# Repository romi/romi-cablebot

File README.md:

# Romi Cablebot (v2)

Documentation coming soon...

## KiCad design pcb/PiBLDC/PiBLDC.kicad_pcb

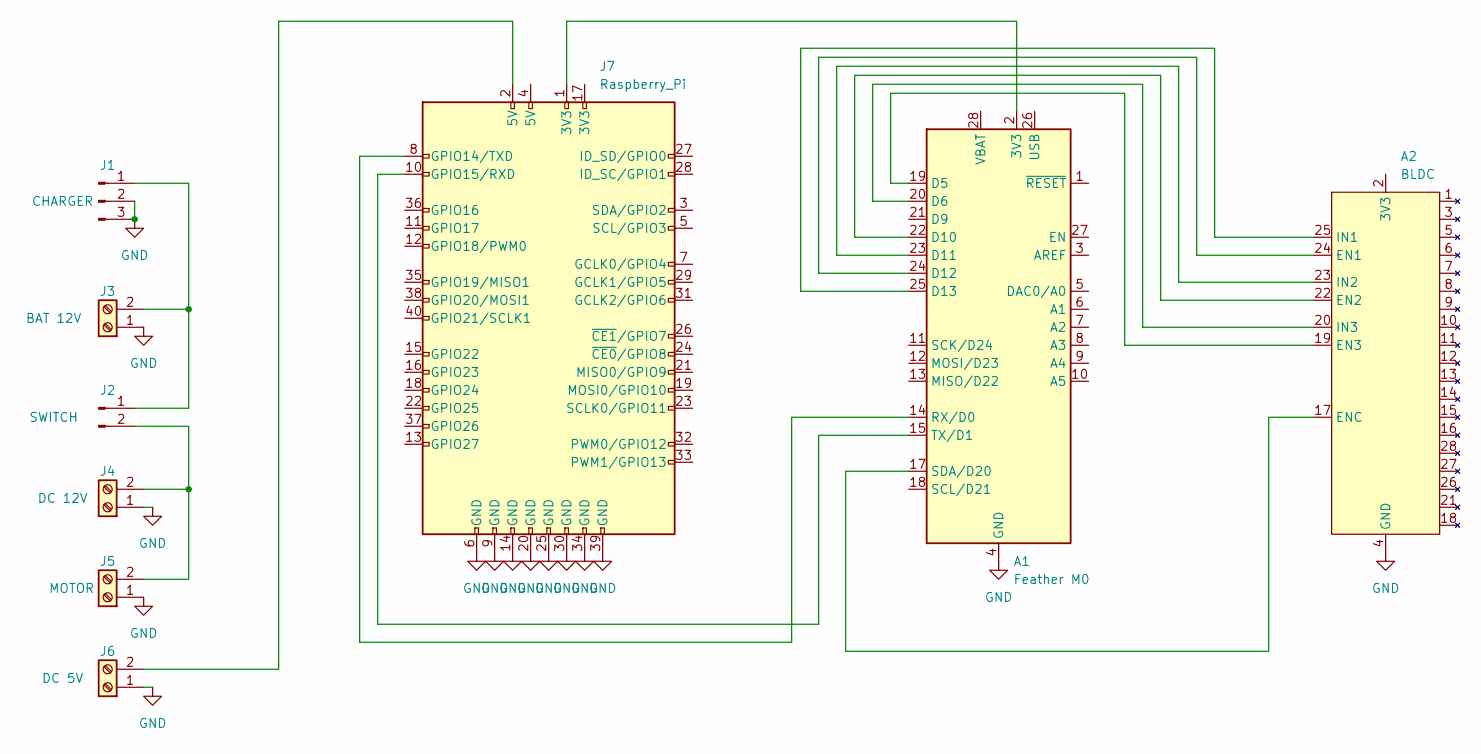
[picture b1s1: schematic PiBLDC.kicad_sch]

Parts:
A1: Feather M0; Adafruit_Feather
A2: BLDC; Adafruit_Feather
J1: CHARGER; Molex_Micro-Fit_3.0_43650-0300_1x03_P3.00mm_Horizontal
J2: SWITCH; Molex_Micro-Fit_3.0_43650-0200_1x02_P3.00mm_Horizontal
J3: BAT 12V; TerminalBlock_Phoenix_PT-1,5-2-3.5-H_1x02_P3.50mm_Horizontal
J4: DC 12V; TerminalBlock_Phoenix_PT-1,5-2-3.5-H_1x02_P3.50mm_Horizontal
J5: MOTOR; TerminalBlock_Phoenix_PT-1,5-2-3.5-H_1x02_P3.50mm_Horizontal
J6: DC 5V; TerminalBlock_Phoenix_PT-1,5-2-3.5-H_1x02_P3.50mm_Horizontal
J7: Raspberry_Pi; PinHeader_2x20_P2.54mm_Vertical

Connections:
GND: A1.4 (GND), A1.16 (GND), A2.4 (GND), J1.2, J1.3, J3.1, J4.1, J5.1, J6.1, J7.6 (GND), J7.9 (GND), J7.14 (GND), J7.20 (GND), J7.25 (GND), J7.30 (GND), J7.34 (GND), J7.39 (GND)
unnamed: A1.2 (3V3), J7.1 (3V3)
unnamed: A1.14 (RX/D0), J7.8 (GPIO14/TXD)
unnamed: A1.15 (TX/D1), J7.10 (GPIO15/RXD)
unnamed: A1.17 (SDA/D20), A2.17 (ENC)
unnamed: A1.19 (D5), A2.19 (EN3)
unnamed: A1.20 (D6), A2.20 (IN3)
unnamed: A1.22 (D10), A2.22 (EN2)
unnamed: A1.23 (D11), A2.23 (IN2)
unnamed: A1.24 (D12), A2.24 (EN1)
unnamed: A1.25 (D13), A2.25 (IN1)
unnamed: J1.1, J2.1, J3.2
unnamed: J2.2, J4.2, J5.2
unnamed: J6.2, J7.2 (5V)

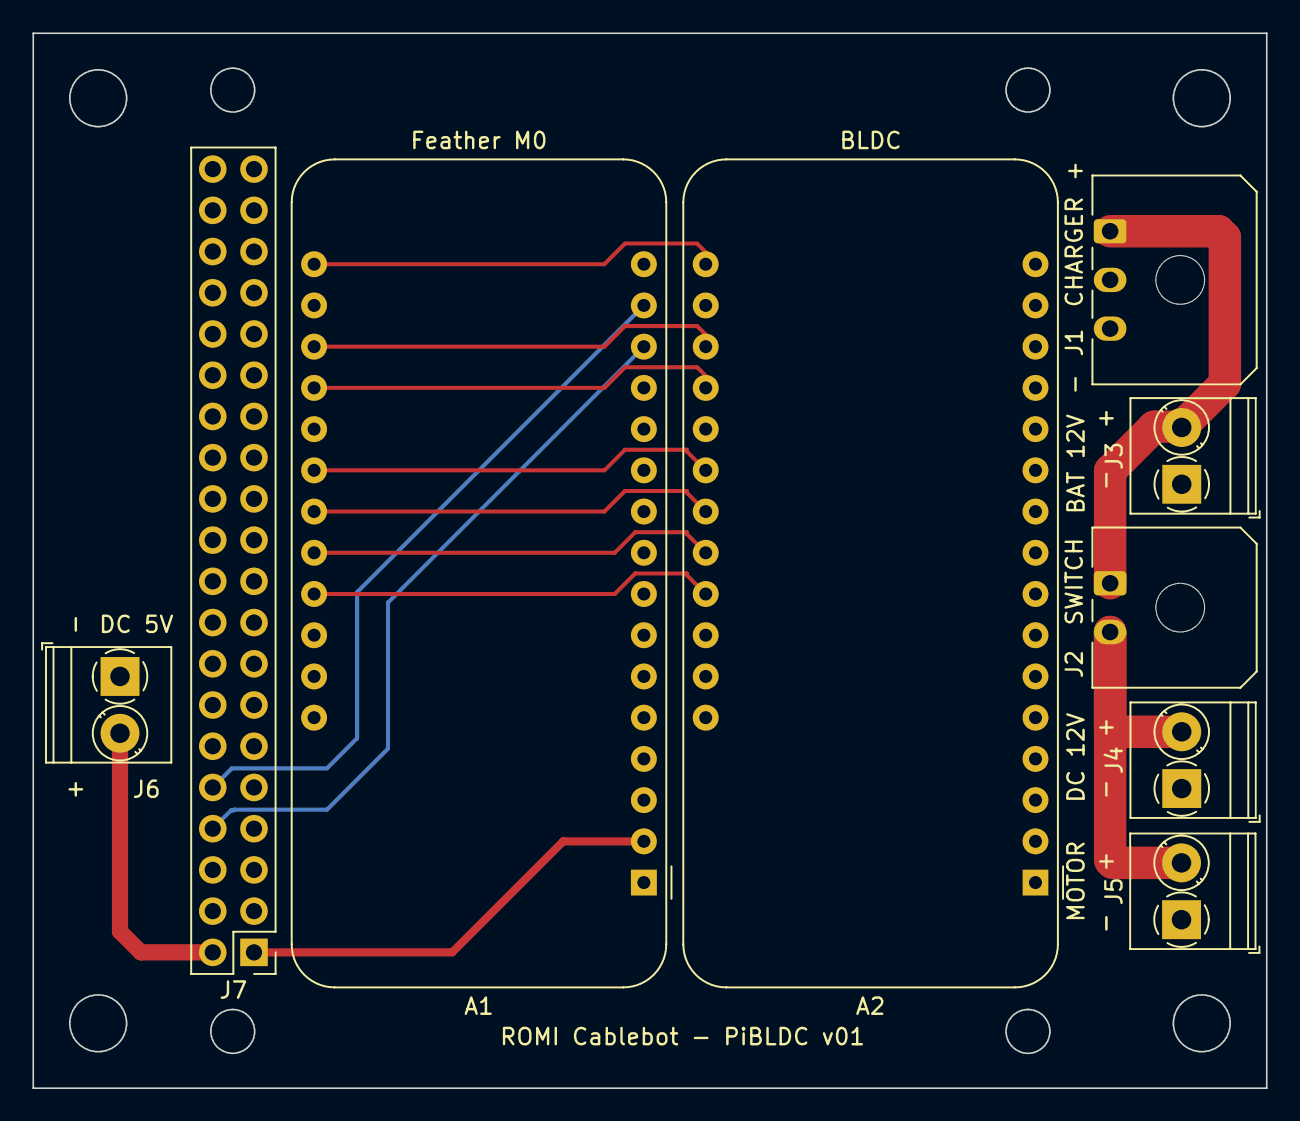
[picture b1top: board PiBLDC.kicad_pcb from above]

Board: 2 copper layers, 76.0 x 65.0 mm, 9 parts (0 on the bottom side), 14 nets.

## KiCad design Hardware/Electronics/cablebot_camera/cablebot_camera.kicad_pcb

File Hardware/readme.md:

# Cablebot hardware

## Head
### 3d printed PLA

|       |                                                                      |
| :---: | ---                                                                  |
| 1x    | [Encoder cap](./3d-Print/Cablebot-Encoder_cap.stl)                   |
| 1x    | [Head separator front](./3d-Print/Cablebot-Head_separator_front.stl) |
| 1x    | [Head separator up](./3d-Print/Cablebot-Head_separator_up.stl)       |
| 1x    | [Spring holder up](./3d-Print/Cablebot-Spring_holder_Up.stl)         |
| 1x    | [Head separator back](./3d-Print/Cablebot-Head_separator_back.stl)   |
| 1x    | [Encoder holder](./3d-Print/Cablebot-Encoder_holder.stl)             |

### Milled Alucobond

|       |                                                                        |
| :---: | ---                                                                    |
| 1x    | [Head front](./Milled-Alucobond/Cablebot-Head_front.dxf)               |
| 1x    | [Head middle front](./Milled-Alucobond/Cablebot-Head_middle_front.dxf) |
| 1x    | [Head middle back](./Milled-Alucobond/Cablebot-Head_middle_back.dxf)   |
| 1x    | [Head back](./Milled-Alucobond/Cablebot-Head_back.dxf)                 |

## Arms
### 3d printed PLA

|       |                                                                              |
| :---: | ---                                                                          |
| 1x    | [Left arm cap out](./3d-Print/Cablebot-Left_arm_cap_out.stl)                 |
| 1x    | [Pogo pin clip](./3d-Print/Cablebot-Pogo_pin_clip.stl)                       |
| 1x    | [Left arm cap middle](./3d-Print/Cablebot-Left_arm_cap_middle.stl)           |
| 1x    | [Control board pcb holder](./3d-Print/Cablebot-Control_board_pcb_holder.stl) |
| 1x    | [Right arm cap middle](./3d-Print/Cablebot-Right_arm_cap_middle.stl)         |
| 1x    | [Right arm cap out](./3d-Print/Cablebot-Right_arm_cap_out.stl)               |

### Milled Alucobond

|       |                                                                      |
| :---: | ---                                                                  |
| 1x    | [Arm left](./Milled-Alucobond/Cablebot-Arm_left.dxf)                 |
| 4x    | [Arms slider fill](./Milled-Alucobond/Cablebot-Arms_slider_fill.dxf) |
| 4x    | [Arm right](./Milled-Alucobond/Cablebot-Arms_right.dxf)              |

## Hands
### 3d printed PLA

|       |                                                                                    |
| :---: | ---                                                                                |
| 1x    | [Hand end stop trigger left](./3d-Print/Cablebot-Hand_end_stop_trigger_left.stl)   |
| 1x    | [Hand base left](./3d-Print/Cablebot-Hand_base_left.stl)                           |
| 2x    | [Pulley 608zz](./3d-Print/Cablebot-Pulley_608zz.stl)                               |
| 1x    | [Hand base right](./3d-Print/Cablebot-Hand_base_right.stl)                         |
| 1x    | [Hand end stop trigger right](./3d-Print/Cablebot-Hand_end_stop_trigger_right.stl) |

### Milled Alucobond

|       |                                                                                    |
| :---: | ---                                                                                |
| 1x    | [Hand left out small](./Milled-Alucobond/Cablebot-Hand_left_out_small.dxf)         |
| 1x    | [Hand left middle small](./Milled-Alucobond/Cablebot-Hand_left_middle_small.dxf)   |
| 1x    | [Hand front left](./Milled-Alucobond/Cablebot-Hand_front_left.dxf)                 |
| 1x    | [Hand right out small](./Milled-Alucobond/Cablebot-Hand_right_out_small.dxf)       |
| 1x    | [Hand right middle small](./Milled-Alucobond/Cablebot-Hand_right_middle_small.dxf) |
| 1x    | [Hand front right](./Milled-Alucobond/Cablebot-Hand_front_right.dxf)               |
| 1x    | [Hand left out big](./Milled-Alucobond/Cablebot-Hand_left_out_big.dxf)             |
| 1x    | [Hand left middle big](./Milled-Alucobond/Cablebot-Hand_left_middle_big.dxf)       |
| 1x    | [Hand right out big](./Milled-Alucobond/Cablebot-Hand_right_out_big.dxf)           |
| 1x    | [Hand right middle big](./Milled-Alucobond/Cablebot-Hand_right_middle_big.dxf)     |

Just one set is needed either _small_ or _big_, depending on cable tension (big is better for high tension).

## Body 
### 3d printed PLA

|       |                                                                  |
| :---: | ---                                                              |
| 1x    | [Cable bridge left](./3d-Print/Cablebot-Cable_bridge_left.stl)   |
| 1x    | [Spring holder down](./3d-Print/Cablebot-Spring_holder_down.stl) |
| 1x    | [Power pcb holder](./3d-Print/Cablebot-Power_pcb_holder.stl)     |
| 1x    | [Cable bridge right](./3d-Print/Cablebot-Cable_bridge_right.stl) |

### Milled Alucobond

|       |                                                                            |
| :---: | ---                                                                        |
| 1x    | [Body cover back](./Milled-Alucobond/Cablebot-Body_cover_back.dxf)         |
| 1x    | [H holder](./Milled-Alucobond/Cablebot-H_holder.dxf)                       |
| 1x    | [Body cover front](./Milled-Alucobond/Cablebot-Body_cover_front.dxf)       |

## Battery module
### 3d printed PLA

|       |                                                                                           |
| :---: | ---                                                                                       |
| 1x    | [Battery cap](./3d-Print/Cablebot-Battery_cap.stl)                                        |
| 1x    | [Battery and BMS box](./3d-Print/Cablebot-Battery_and_BMS_box.stl)                        |
| 1x    | [Battery connector top](./3d-Print/Cablebot-Battery_connector_top.stl)                    |
| 1x    | [Battery connector bottom](./3d-Print/Cablebot-Battery_connector_bottom.stl)              |

### Milled Alucobond

|       |                                                                            |
| :---: | ---                                                                        |
| 1x    | [Battery cover](./Milled-Alucobond/Cablebot-Battery_cover.dxf)             |

## Camera module
### 3d printed PLA

|       |                                                                     |
| :---: | ---                                                                 |
| 1x    | [Bearing cap](./3d-Print/Camera_module-Bearing_cap.stl)             |
| 1x    | [Main cap](./3d-Print/Camera_module-Main_Cap.stl)                   |
| 1x    | [Pcb holder](./3d-Print/Camera_module-PCB_holder.stl)               |
| 1x    | [Top connector cap](./3d-Print/Camera_module-Top_connector_cap.stl) |
| 1x    | [Corner motor top](./3d-Print/Camera_module-Corner_motor_top.stl)   |

### Milled Alucobond

|       |                                                                     |
| :---: | ---                                                                 |
| 1x    | [Holder top](./Milled-Alucobond/Camera_module-Holder_top.dxf)       |
| 1x    | [Holder bottom](./Milled-Alucobond/Camera_module-Holder_bottom.dxf) |
| 1x    | [Holder camera](./Milled-Alucobond/Camera_module-Holder_camera.dxf) |

## Charging Station hardware

### 3d printed PLA

|		|																	|
| :---: | --- 																|
| 1x 	| [Arc](./3d-Print/Charging_station-Arc.stl)						|
| 1x 	| [Hold roof](./3d-Print/Charging_station-Hold_roof.stl) 			|
| 2x 	| [Caps](./3d-Print/Charging_station-Cap.stl) 						|
| 4x 	| [Cap separator](./3d-Print/Charging_station-Cap_separator.stl) 	|

### Milled Alucobond

|       |                                                                     |
| :---: | ---                                                                 |
| 1x    | [Back](./Milled-Alucobond/Charging_station-Back.dxf)       		  |
| 1x    | [Roof](./Milled-Alucobond/Charging_station-Roof.dxf) 		   		  |
| 1x    | [Side left](./Milled-Alucobond/Charging_station-Sides.dxf)  		  |
| 1x    | [Side right](./Milled-Alucobond/Charging_station-Sides.dxf) 		  |

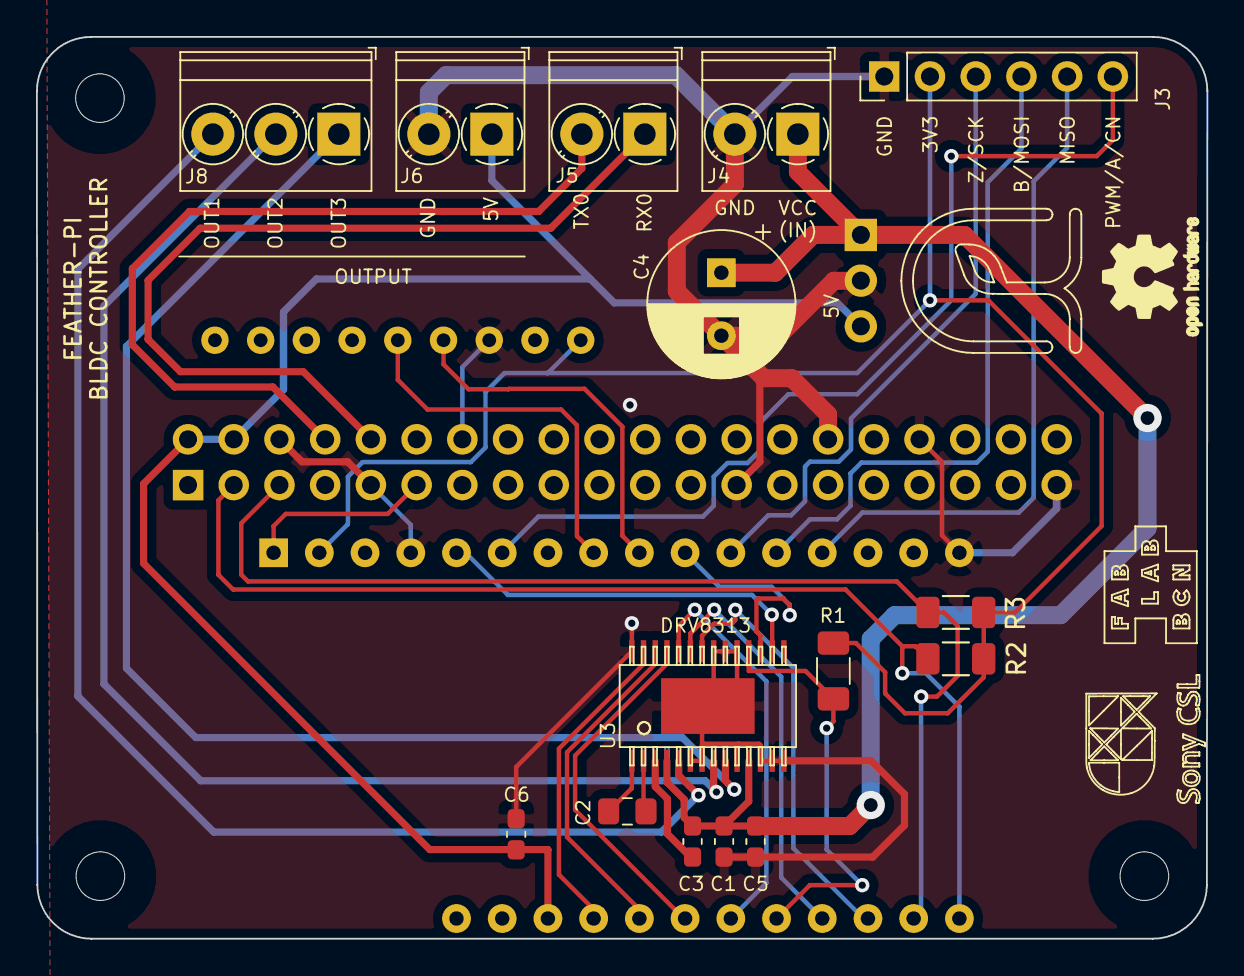
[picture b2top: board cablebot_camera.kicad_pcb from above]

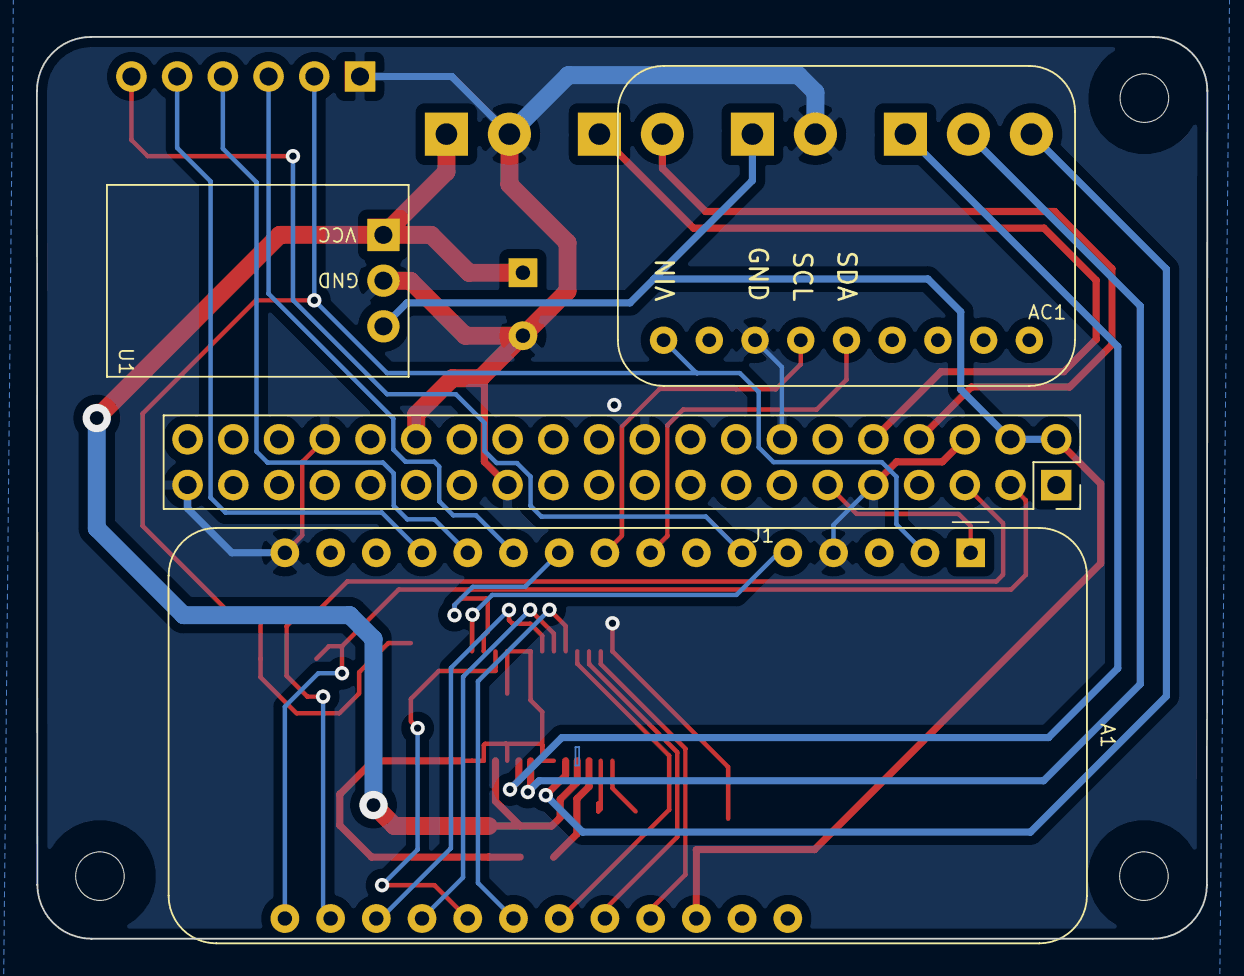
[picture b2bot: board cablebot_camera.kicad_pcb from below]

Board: 2 copper layers, 65.0 x 50.1 mm, 26 parts (4 on the bottom side), 31 nets.

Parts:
A1: Adafruit_Feather_M0_Express; Adafruit_Feather
AC1: ACCEL; Adafruit-LSM6DSOX-PCB
C1, C3, C5, C6: 0.1uF; C_0603_1608Metric_Pad1.08x0.95mm_HandSolder
C2: 0.01uF; C_0805_2012Metric_Pad1.18x1.45mm_HandSolder
C4: 100uF; CP_Radial_D8.0mm_P3.50mm
H3, H4, H6: MountingHole; MountingHole_2.7mm_M2.5_uHAT_RPi
J1: GPIO_CONNECTOR; PinSocket_2x20_P2.54mm_Vertical_Centered_Anchor
J3: Conn_01x06_Male; PinHeader_1x06_P2.54mm_Vertical
J4, J5, J6: Screw_Terminal_01x02; TerminalBlock_Phoenix_PT-1,5-2-3.5-H_1x02_P3.50mm_Horizontal
J8: Screw_Terminal_01x03; TerminalBlock_Phoenix_PT-1,5-3-3.5-H_1x03_P3.50mm_Horizontal
LOGO1: Logo_Open_Hardware_Small; OSHW-Logo2_7.3x6mm_SilkScreen
LOGO2: fablab
LOGO3: ROMI; ROMI_LOGO
LOGO4: SONYLOGO; SONY_CSL_LOGO
R1, R2, R3: 10kΩ; R_1206_3216Metric_Pad1.30x1.75mm_HandSolder
U1: OKI-78SR-5_1.5-W36-C; Converter_DCDC_Murata_OKI-78SR_Horizontal
U3: DRV8313; SquantorTexasInstruments-HTSSOP-28

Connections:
3V3: A1.2, AC1.1, J3.2, R1.2, R2.1, R3.1
5V: A1.26, C6.2, J1.2, J1.4, J6.1, U1.3
+3V3: J1.1, J1.17
CN_PWM_A: A1.6, J3.6
EN1: A1.24, U3.26
EN2: A1.22, U3.24
EN3: A1.19, U3.22
FAULT: A1.21, R1.1, U3.18
FEATHER_RESET: A1.1, J1.11
GND: A1.4, A1.16, AC1.3, C1.1, C4.2, C5.1, C6.1, J1.6, J1.9, J1.14, J1.20, J1.25, J1.30, J1.34, J1.39, J3.1, J4.2, J6.2, U1.2, U3.6, U3.7, U3.10, U3.12, U3.13, U3.14, U3.19, U3.20, U3.21, U3.28, U3.PAD
IN1: A1.25, U3.27
IN2: A1.23, U3.25
IN3: A1.20, U3.23
MISO: A1.13, J3.5
MOSI_B: A1.12, J3.4
unnamed: C2.1, U3.1
unnamed: C2.2, U3.2
unnamed: C3.2, U3.3
OUT1: J8.3, U3.5
OUT2: J8.2, U3.8
OUT3: J8.1, U3.9
RESET: A1.5, U3.16
RX0: J1.10, J5.1
SCK_Z: A1.11, J3.3
SCL: A1.18, J1.5, R3.2
SCL_IMU: A1.9, AC1.4
SDA: A1.17, J1.3, R2.2
SDA_IMU: A1.8, AC1.5
SLEEP: A1.10, U3.17
TX0: J1.8, J5.2
VCC: C1.2, C3.1, C4.1, C5.2, J4.1, U1.1, U3.4, U3.11

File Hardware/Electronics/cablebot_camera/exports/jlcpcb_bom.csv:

Comment,Designator,Footprint,LCSC
"Adafruit_Feather_M0_Express","A1","Module:Adafruit_Feather",""
"ACCEL","AC1","fab:Adafruit-LSM6DSOX-PCB",""
"0.01uF","C2","Capacitor_SMD:C_0805_2012Metric_Pad1.18x1.45mm_HandSolder","C28233"
"0.1uF","C1,C3,C5,C6","Capacitor_SMD:C_0603_1608Metric_Pad1.08x0.95mm_HandSolder","C14663"
"100uF","C4","Capacitor_THT:CP_Radial_D8.0mm_P3.50mm",""
"MountingHole","H3,H4,H6","lib:MountingHole_2.7mm_M2.5_uHAT_RPi",""
"GPIO_CONNECTOR","J1","lib:PinSocket_2x20_P2.54mm_Vertical_Centered_Anchor",""
"Conn_01x06_Male","J3","Connector_PinHeader_2.54mm:PinHeader_1x06_P2.54mm_Vertical",""
"Screw_Terminal_01x02","J4,J5,J6","TerminalBlock_Phoenix:TerminalBlock_Phoenix_PT-1,5-2-3.5-H_1x02_P3.50mm_Horizontal",""
"Screw_Terminal_01x03","J8","TerminalBlock_Phoenix:TerminalBlock_Phoenix_PT-1,5-3-3.5-H_1x03_P3.50mm_Horizontal",""
"Logo_Open_Hardware_Small","LOGO1","Symbol:OSHW-Logo2_7.3x6mm_SilkScreen",""
"fablab","LOGO2","logos:fablab",""
"ROMI","LOGO3","logos:ROMI_LOGO",""
"SONYLOGO","LOGO4","logos:SONY_CSL_LOGO",""
"10kΩ","R1,R2,R3","Resistor_SMD:R_1206_3216Metric_Pad1.30x1.75mm_HandSolder",""
"OKI-78SR-5_1.5-W36-C","U1","Converter_DCDC:Converter_DCDC_Murata_OKI-78SR_Horizontal",""
"DRV8313","U3","SquantorTexasInstruments:SquantorTexasInstruments-HTSSOP-28","C92482"

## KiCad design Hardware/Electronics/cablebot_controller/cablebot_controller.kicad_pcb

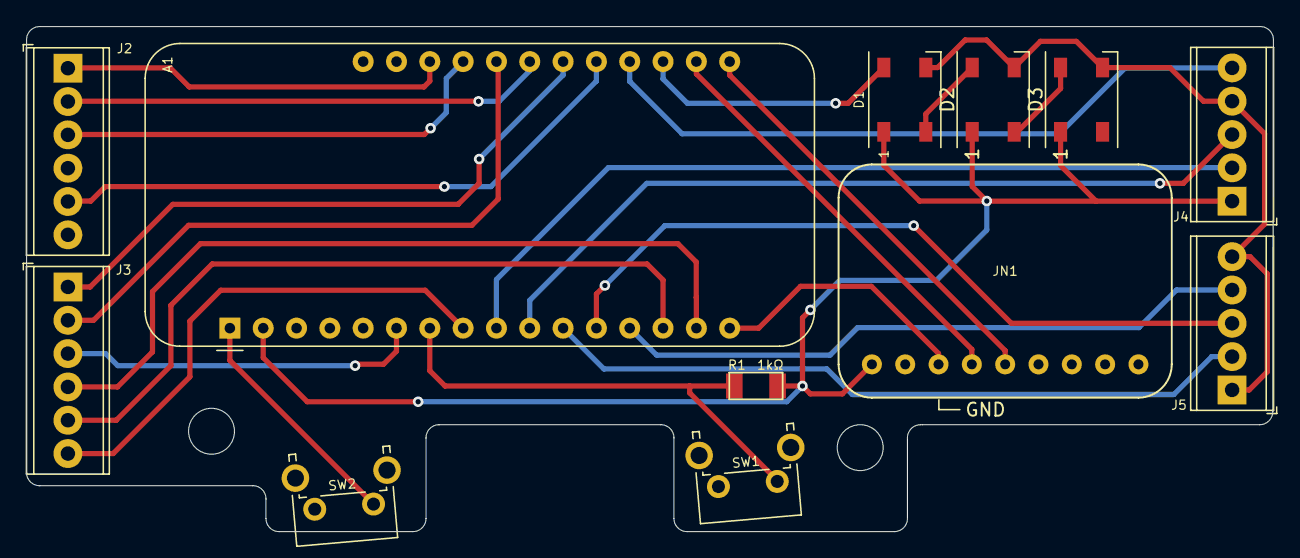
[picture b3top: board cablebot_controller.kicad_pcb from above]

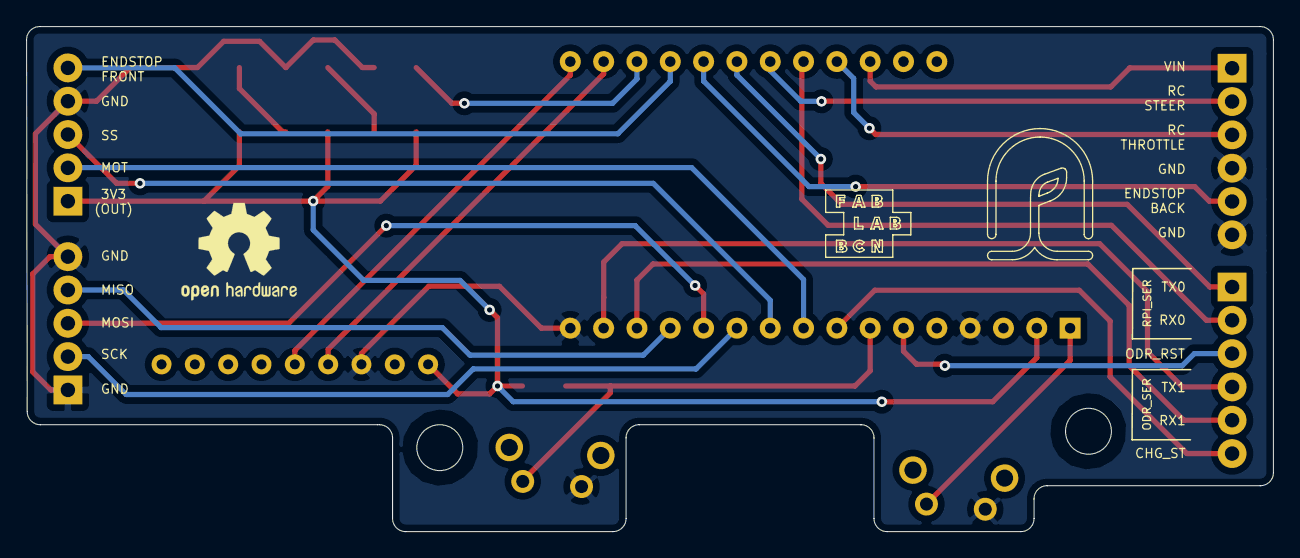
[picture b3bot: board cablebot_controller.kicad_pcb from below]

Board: 2 copper layers, 95.1 x 38.5 mm, 15 parts (3 on the bottom side), 25 nets.

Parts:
A1: Adafruit_Feather_M0_Basic_Proto; Adafruit_Feather
D1, D2, D3: WS2812B; LED_WS2812B_PLCC4_5.0x5.0mm_P3.2mm
J2, J3: Screw_Terminal_01x06; TerminalBlock_Phoenix_MPT-0,5-6-2.54_1x06_P2.54mm_Horizontal
J4, J5: Screw_Terminal_01x05; TerminalBlock_Phoenix_MPT-0,5-5-2.54_1x05_P2.54mm_Horizontal
JN1: ACCEL; Adafruit-LSM6DSOX-PCB
OSH1: Logo_Open_Hardware_Small; OSHW-Logo2_9.8x8mm_SilkScreen
R1: 1kΩ; fab-R1206FAB
SW1: SW_SPST; SW_Tactile_SPST_Angled_PTS645Vx83-2LFS
SW2: SW_SPST; SW_Tactile_SPST_Angled_PTS645Vx58-2LFS
U1: fablab
U2: romi; ROMI_LOGO

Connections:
3V3: A1.2, D1.1, D2.1, D3.1, J4.1, JN1.1, R1.1
5V: A1.26, J2.1
ADNS_MOT: A1.9, J4.2
ADNS_SS: A1.10, J4.3
CHG_ST_HOME: A1.8, J3.6
ENDSTOP_BACK: A1.21, J2.5
ENDSTOP_FRONT: A1.20, J4.5
GND: A1.4, A1.16, D1.3, D2.3, D3.3, J2.4, J2.6, J4.4, J5.1, J5.5, JN1.3, SW1.2, SW2.2
LED_DIN: A1.19, D1.4
MISO: A1.13, J5.4
MOSI: A1.12, J5.3
unnamed: D1.2, D2.4
unnamed: D2.2, D3.4
ODRIVE_RST: A1.6, J3.3
RC_STR: A1.23, J2.2
RC_THROTTLE: A1.25, J2.3
RST_BUTTON: A1.1, SW2.1
RX0: A1.24, J3.2
RX1: A1.14, J3.5
SCK: A1.11, J5.2
SCL: A1.18, JN1.4
SDA: A1.17, JN1.5
TX0: A1.22, J3.1
TX1: A1.15, J3.4
USER_BUTTON: A1.7, R1.2, SW1.1

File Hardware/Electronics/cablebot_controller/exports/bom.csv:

"Id";"Designator";"Package";"Quantity";"Designation";"Supplier and ref";
1;"D3,D2,D1";"LED_WS2812B_PLCC4_5.0x5.0mm_P3.2mm";3;"WS2812B";;;
2;"OSH1";"OSHW-Logo2_9.8x8mm_SilkScreen";1;"Logo_Open_Hardware_Small";;;
3;"U2";"ROMI_LOGO";1;"romi";;;
4;"U1";"fablab";1;"fablab";;;
5;"SW2";"SW_Tactile_SPST_Angled_PTS645Vx58-2LFS";1;"SW_SPST";;;
6;"A1";"Adafruit_Feather";1;"Adafruit_Feather_M0_Basic_Proto";;;
7;"J5,J4";"TerminalBlock_Phoenix_MPT-0,5-5-2.54_1x05_P2.54mm_Horizontal";2;"Screw_Terminal_01x05";;;
8;"J3,J2";"TerminalBlock_Phoenix_MPT-0,5-6-2.54_1x06_P2.54mm_Horizontal";2;"Screw_Terminal_01x06";;;
9;"SW1";"SW_Tactile_SPST_Angled_PTS645Vx83-2LFS";1;"SW_SPST";;;
10;"R1";"fab-R1206FAB";1;"1kΩ";;;
11;"JN1";"Adafruit-LSM6DSOX-PCB";1;"ACCEL";;;

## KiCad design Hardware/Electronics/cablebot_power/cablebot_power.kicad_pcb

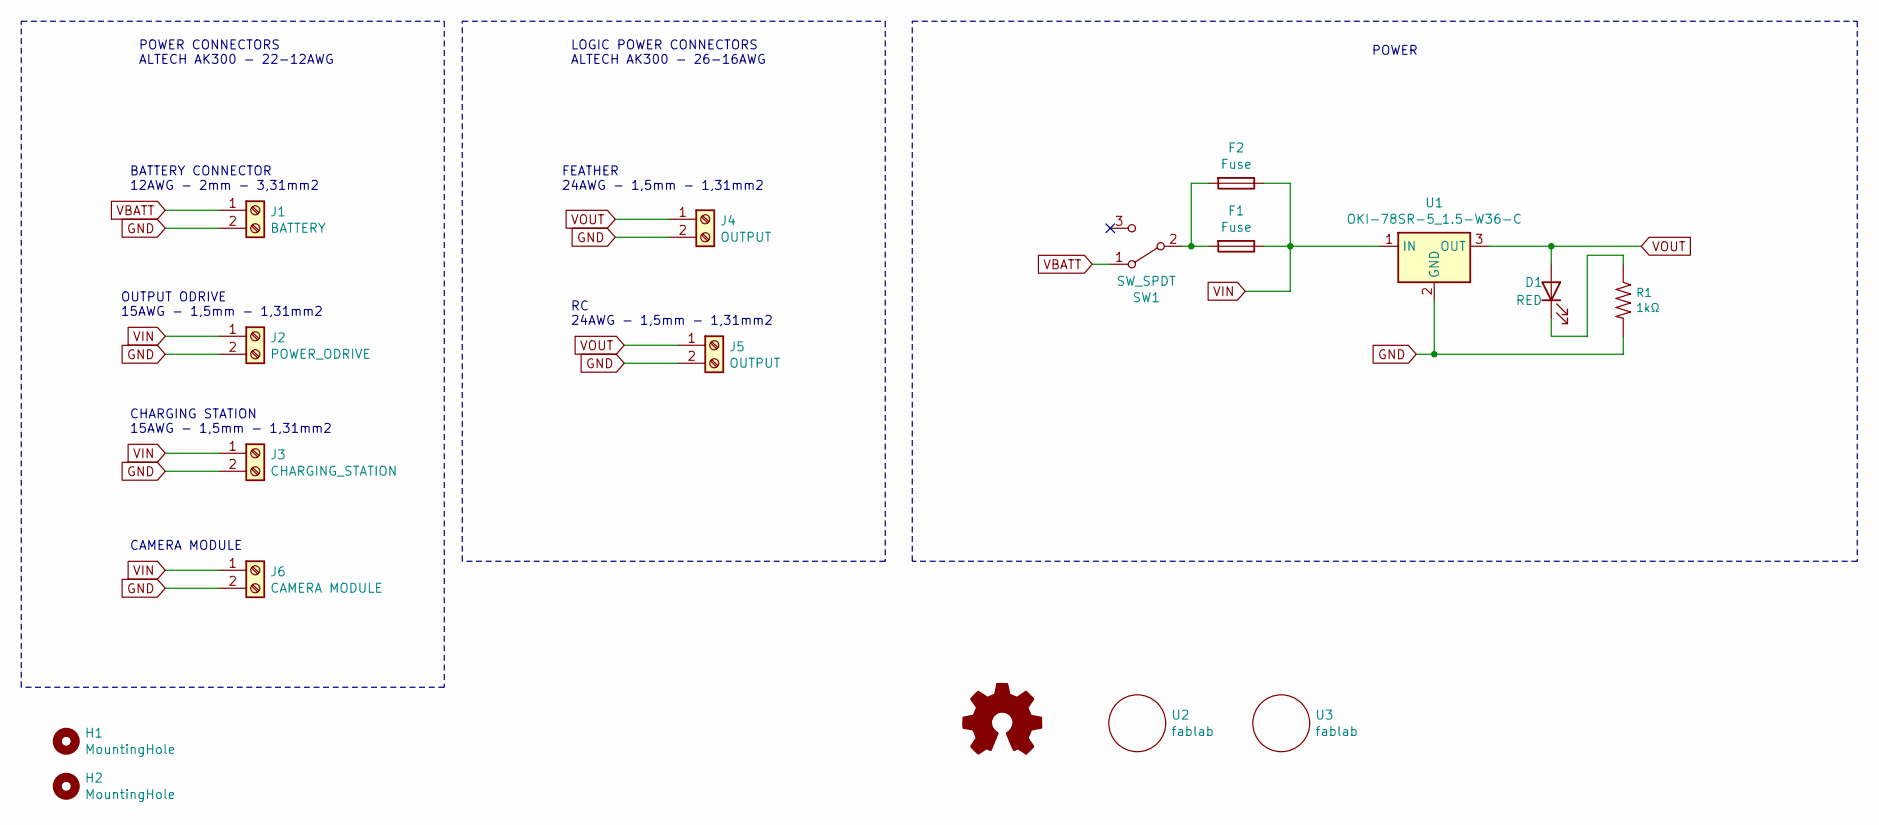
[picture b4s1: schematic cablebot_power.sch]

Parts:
D1: RED; fab-LED1206FAB
F1: Fuse; Fuseholder_Littelfuse_Nano2_154x
F2: Fuse; GENERIC_4010_10228
H1, H2: MountingHole; MountingHole_3.2mm_M3
J1: BATTERY; TerminalBlock_Altech_AK300-2_P5.00mm; Mouser Ref 845-30.602/BLU
J2: POWER_ODRIVE; TerminalBlock_Altech_AK300-2_P5.00mm; Mouser Ref 845-30.602/BLU
J3: CHARGING_STATION; TerminalBlock_Altech_AK300-2_P5.00mm; Mouser Ref 845-30.602/BLU
J4, J5: OUTPUT; TerminalBlock_Phoenix_PT-1,5-2-3.5-H_1x02_P3.50mm_Horizontal; Mouser Ref 651-1985807
J6: CAMERA MODULE; TerminalBlock_Phoenix_PT-1,5-2-3.5-H_1x02_P3.50mm_Horizontal; Mouser Ref 651-1985807
OSH1: Logo_Open_Hardware_Small; OSHW-Logo2_7.3x6mm_SilkScreen
R1: 1kΩ; fab-R1206FAB
SW1: SW_SPDT; TerminalBlock_Altech_AK300-2_P5.00mm
U1: OKI-78SR-5_1.5-W36-C; Converter_DCDC_Murata_OKI-78SR_Horizontal; Mouser Ref 580-OK78SR5/1.5W36EC
U2: fablab
U3: fablab; ROMI_LOGO

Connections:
GND: J1.2, J2.2, J3.2, J4.2, J5.2, J6.2, R1.2, U1.2 (GND)
unnamed: D1.1 (K), R1.1
unnamed: F1.2, F2.2, SW1.2 (B)
VBATT: J1.1, SW1.1 (A)
VIN: F1.1, F2.1, J2.1, J3.1, J6.1, U1.1 (IN)
VOUT: D1.2 (A), J4.1, J5.1, U1.3 (OUT)

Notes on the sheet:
BATTERY CONNECTOR 12AWG - 2mm - 3,31mm2
OUTPUT ODRIVE 15AWG - 1,5mm - 1,31mm2
POWER CONNECTORS ALTECH AK300 - 22-12AWG
FEATHER 24AWG - 1,5mm - 1,31mm2
RC 24AWG - 1,5mm - 1,31mm2
CHARGING STATION 15AWG - 1,5mm - 1,31mm2
LOGIC POWER CONNECTORS ALTECH AK300 - 26-16AWG
CAMERA MODULE
POWER

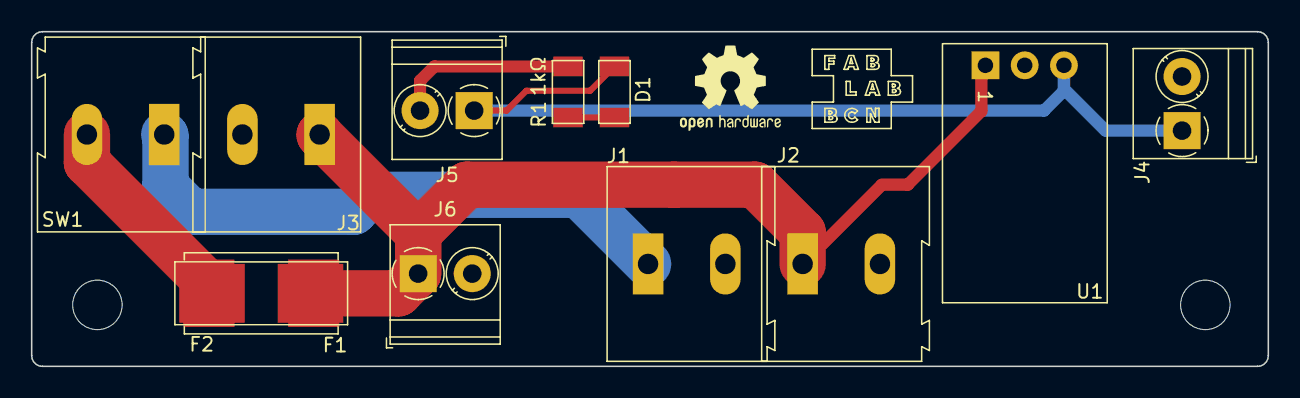
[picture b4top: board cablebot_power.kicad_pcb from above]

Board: 2 copper layers, 80.0 x 21.7 mm, 17 parts (1 on the bottom side), 6 nets.

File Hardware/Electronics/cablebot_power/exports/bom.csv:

"Id";"Designator";"Package";"Quantity";"Designation";"Supplier and ref";
1;"U3";"ROMI_LOGO";1;"fablab";;;
2;"U2";"fablab";1;"fablab";;;
3;"H2,H1";"MountingHole_3.2mm_M3";2;"MountingHole";;;
4;"J6";"TerminalBlock_Phoenix_PT-1,5-2-3.5-H_1x02_P3.50mm_Horizontal";1;"CAMERA MODULE";;;
5;"OSH1";"OSHW-Logo2_7.3x6mm_SilkScreen";1;"Logo_Open_Hardware_Small";;;
6;"SW1";"TerminalBlock_Altech_AK300-2_P5.00mm";1;"SW_SPDT";;;
7;"F2";"GENERIC_4010_10228";1;"Fuse";;;
8;"F1";"Fuseholder_Littelfuse_Nano2_154x";1;"Fuse";;;
9;"U1";"Converter_DCDC_Murata_OKI-78SR_Horizontal";1;"OKI-78SR-5_1.5-W36-C";;;
10;"R1";"fab-R1206FAB";1;"1kΩ";;;
11;"D1";"fab-LED1206FAB";1;"RED";;;
12;"J5,J4";"TerminalBlock_Phoenix_PT-1,5-2-3.5-H_1x02_P3.50mm_Horizontal";2;"OUTPUT";;;
13;"J3";"TerminalBlock_Altech_AK300-2_P5.00mm";1;"CHARGING_STATION";;;
14;"J2";"TerminalBlock_Altech_AK300-2_P5.00mm";1;"POWER_ODRIVE";;;
15;"J1";"TerminalBlock_Altech_AK300-2_P5.00mm";1;"BATTERY";;;

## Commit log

2021-04-27 Saved work before changing motor
2022-02-10 Added STL for 3d printed parts
2022-02-14 Added Odrive and Button libraries
2022-02-14 Updated build instructions (removed nano board)
2022-02-14 Removed old Odrive Arduino library
2022-02-14 Started Romi Odrive library integration
2022-03-02 Added milled parts and readme, naming updates
2022-03-02 Fix Readme img links
2022-06-02 added battery check
2022-07-01 Enable SWD flashing
2022-07-01 Added PCBS
2022-08-01 Updated files for 8 pin Camera Module connector
2022-08-01 Added blender file
2022-08-23 Updated hand base models with more stable version
2022-08-23 Small update on cable management on right bridge
2022-08-23 Added off switch signal engraved in 3d model
2022-08-23 Easier Raspberry installation on Camera module
2022-08-23 Updated 3d model images
2022-08-23 Updated images
2022-08-23 More image updates
2022-08-23 More images updates
2022-08-23 Image update
2022-08-23 Remove image black borders
2022-08-23 Global images update
2022-08-24 Corrected 3d model orientation
2022-12-16 Battery connector changed to 6 pin header
2022-12-16 Added Charging Station files
2022-12-16 Updated Blender file mostly Charging station work
2022-12-23 debugging
2023-08-24 importing new version
2023-08-24 removing v1
2023-08-24 importing v2
2024-06-25 Cam-Mount
2024-06-27 add Cablecam-Cam-Mount and Cablecam-Window3
2024-06-27 add commentary Cablecam.scad
2025-11-03 importing scripts
2025-11-03 importing v3

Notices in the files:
Hardware/Electronics/cablebot_camera/cablebot_camera.kicad_pcb:
This PCB design is licensed under MIT Open Source License.
pcb/PiBLDC/PiBLDC.kicad_pcb:
https://creativecommons.org/licenses/by-sa/4.0
License: Creative Commons BY-SA 4.0
